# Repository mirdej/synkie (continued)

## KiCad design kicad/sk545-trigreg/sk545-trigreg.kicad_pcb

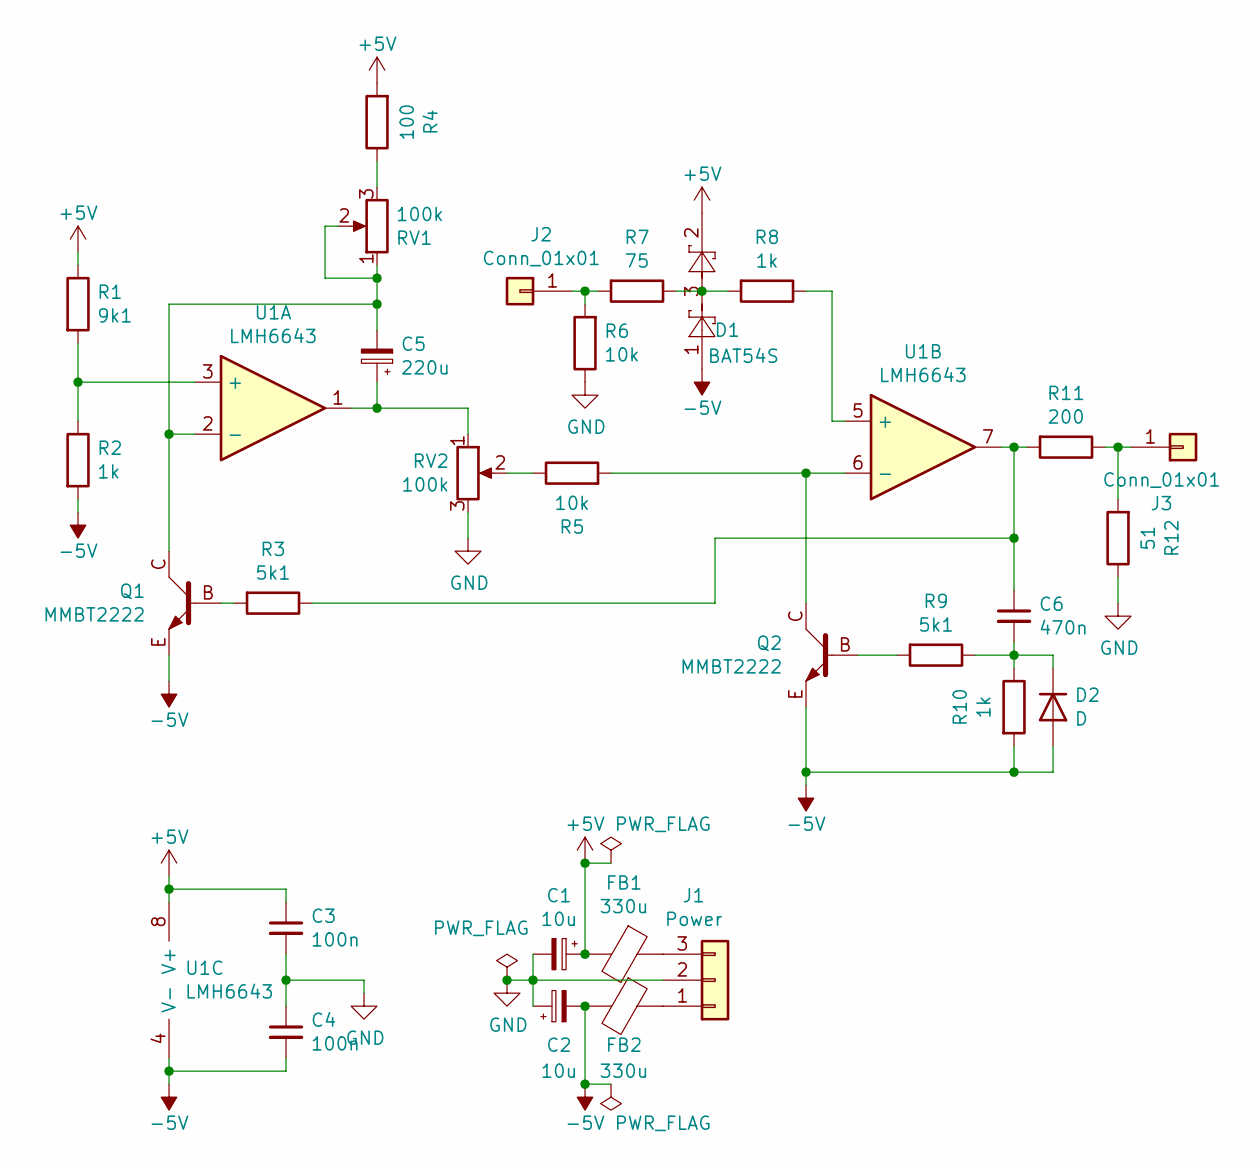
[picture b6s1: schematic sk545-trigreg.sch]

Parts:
C1, C2: 10u; CP_EIA-3528-21_Kemet-B_Pad1.50x2.35mm_HandSolder
C3, C4: 100n; C_0805_2012Metric_Pad1.15x1.40mm_HandSolder
C5: 220u; CP_EIA-7361-38_AVX-V_Pad2.18x3.30mm_HandSolder
C6: 470n; C_0805_2012Metric_Pad1.15x1.40mm_HandSolder
D1: BAT54S; SOT-23
D2: D; D_SOT-23_ANK
FB1, FB2: 330u; L_1206_3216Metric_Pad1.42x1.75mm_HandSolder
J1: Power; Molex_KK-254_AE-6410-03A_1x03_P2.54mm_Vertical
J2, J3: Conn_01x01; Solderpad_1mm
Q1, Q2: MMBT2222; SOT-23_BEC
R1: 9k1; R_0805_2012Metric_Pad1.15x1.40mm_HandSolder
R2, R8, R10: 1k; R_0805_2012Metric_Pad1.15x1.40mm_HandSolder
R3, R9: 5k1; R_0805_2012Metric_Pad1.15x1.40mm_HandSolder
R4: 100; R_0805_2012Metric_Pad1.15x1.40mm_HandSolder
R5, R6: 10k; R_0805_2012Metric_Pad1.15x1.40mm_HandSolder
R7: 75; R_0805_2012Metric_Pad1.15x1.40mm_HandSolder
R11: 200; R_0805_2012Metric_Pad1.15x1.40mm_HandSolder
R12: 51; R_0805_2012Metric_Pad1.15x1.40mm_HandSolder
RV1, RV2: 100k; Potentiometer_Uwe_100k
U1: LMH6643; SOIC-8_3.9x4.9mm_P1.27mm

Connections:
+5V: C1.1, C3.1, D1.2, FB1.2, R1.1, R4.2, U1.8 (V+)
-5V: C2.2, C4.2, D1.1, D2.2 (A), FB2.2, Q1.E, Q2.E, R2.2, R10.2, U1.4 (V-)
GND: C1.2, C2.1, C3.2, C4.1, J1.2, R6.1, R12.1, RV2.3
unnamed: C5.1, RV2.1, U1.1
unnamed: C5.2, Q1.C, RV1.1, RV1.2, U1.2 (-)
unnamed: C6.1, R3.1, R11.2, U1.7
unnamed: C6.2, D2.1 (K), R9.1, R10.1
unnamed: D1.3, R7.1, R8.2
unnamed: FB1.1, J1.3
unnamed: FB2.1, J1.1
unnamed: J2.1, R6.2, R7.2
unnamed: J3.1, R11.1, R12.2
unnamed: Q1.B, R3.2
unnamed: Q2.B, R9.2
unnamed: Q2.C, R5.2, U1.6 (-)
unnamed: R1.2, R2.1, U1.3 (+)
unnamed: R4.1, RV1.3
unnamed: R5.1, RV2.2
unnamed: R8.1, U1.5 (+)

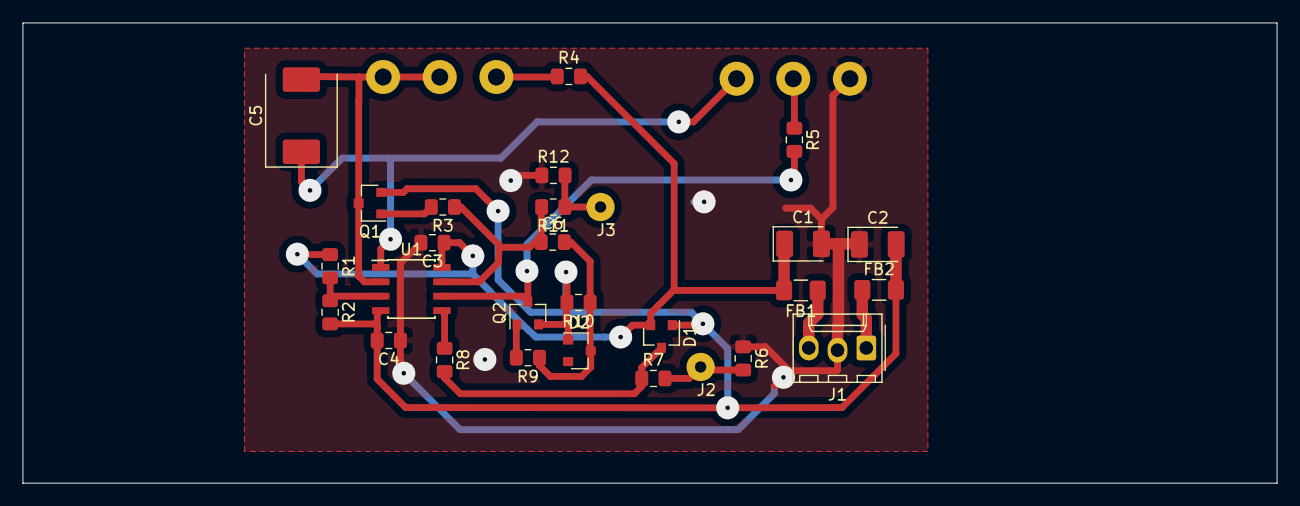
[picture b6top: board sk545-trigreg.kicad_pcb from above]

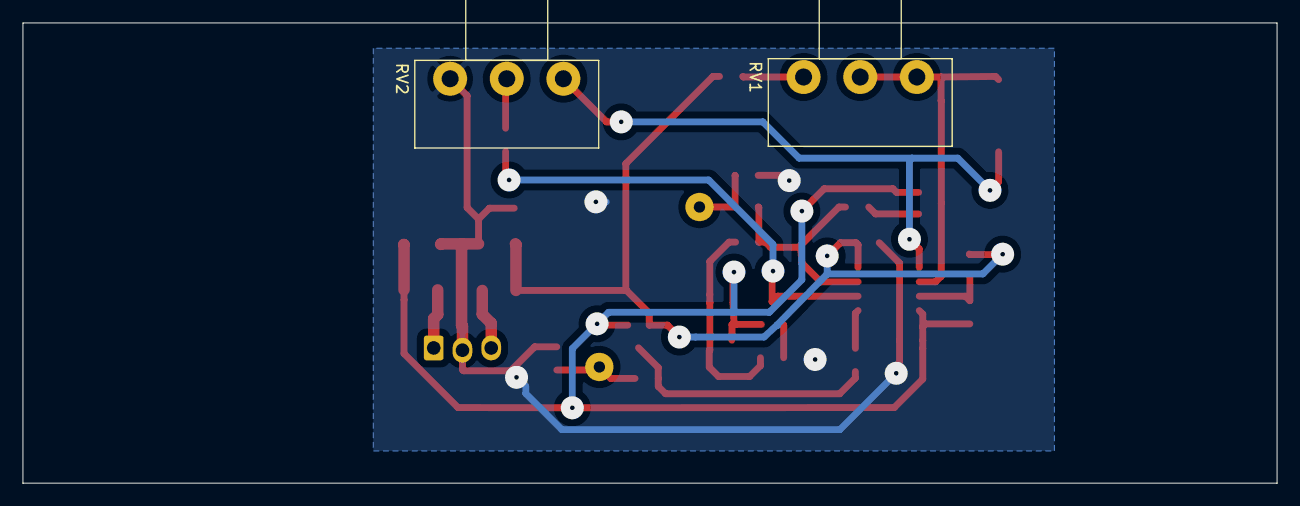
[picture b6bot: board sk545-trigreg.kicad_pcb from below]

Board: 2 copper layers, 110.7 x 40.6 mm, 30 parts (2 on the bottom side), 19 nets.

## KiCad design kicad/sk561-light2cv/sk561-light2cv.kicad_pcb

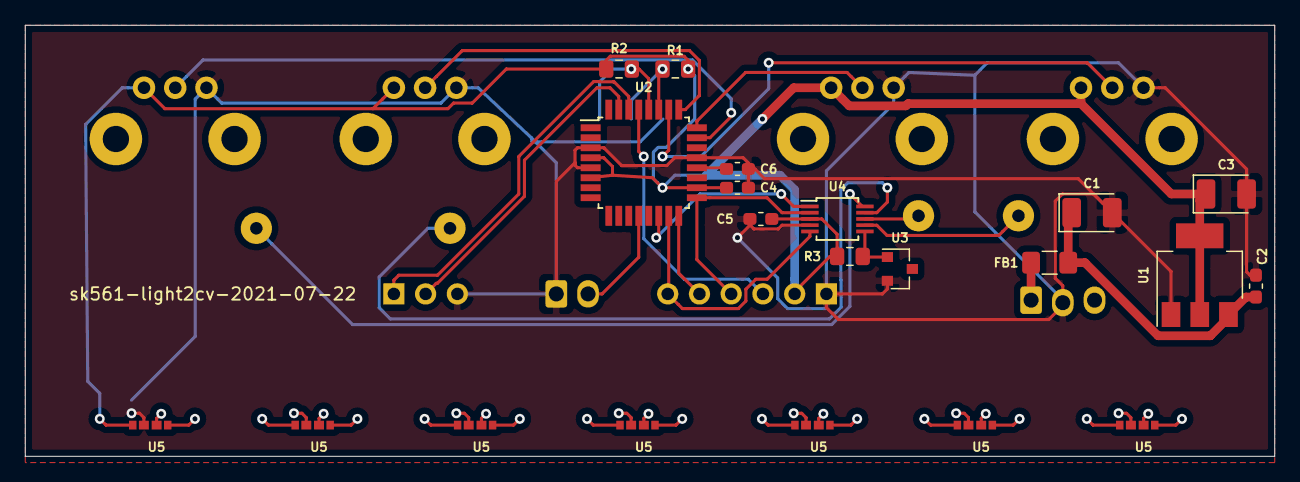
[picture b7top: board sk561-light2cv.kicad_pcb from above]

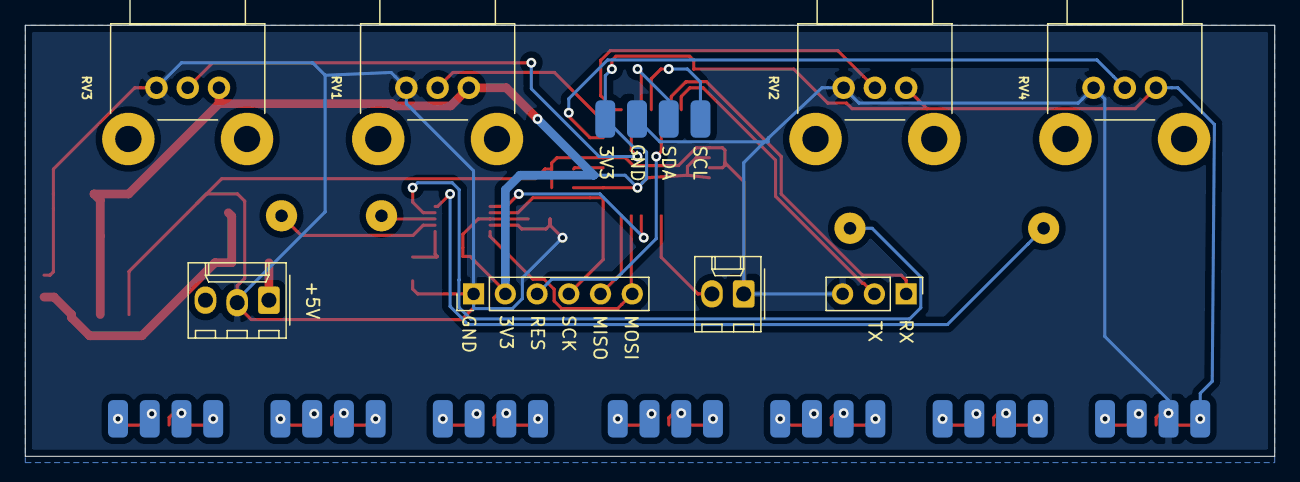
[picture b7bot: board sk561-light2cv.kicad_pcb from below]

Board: 2 copper layers, 100.0 x 34.5 mm, 41 parts (16 on the bottom side), 26 nets.

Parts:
C1, C3: 10u; CP_EIA-3528-21_Kemet-B_Pad1.50x2.35mm_HandSolder
C2, C4, C5, C6: 100n; C_0603_1608Metric_Pad1.05x0.95mm_HandSolder
FB1: Ferrite_Bead; L_1206_3216Metric_Pad1.42x1.75mm_HandSolder
J1: Conn_01x03; Molex_KK-254_AE-6410-03A_1x03_P2.54mm_Vertical
J2: switch; Molex_KK-254_AE-6410-02A_1x02_P2.54mm_Vertical
J3, J5, J6, J7: Conn_01x01; Solderpad_1mm
J4: Serial; PinHeader_1x03_P2.54mm_Vertical
J8: int; smd-4pin
J9, J9#2, J9#3, J9#4, J9#5, J9#6, J9#7: Conn_01x04; smd-4pin
R1, R2: 4k7; R_0805_2012Metric_Pad1.15x1.40mm_HandSolder
R3: 560; R_0805_2012Metric_Pad1.15x1.40mm_HandSolder
RV1, RV2, RV3, RV4: R_POT; Potentiometer_Alps_RK09L_Single_Horizontal
U1: AZ1117-3.3; SOT-223-3_TabPin2
U2: ATmega88-20AU; TQFP-32_7x7mm_P0.8mm
U3: ADR510; SOT-23
U4: MAX5741; MSOP-10_3x3mm_P0.5mm
U5, U5#2, U5#3, U5#4, U5#5, U5#6, U5#7: VEML3328; VEML3328SL
U7: AnymaISP; PinHeader_1x06_P2.54mm_Vertical

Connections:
+3V3: C3.1, C4.1, C5.1, J8.1, J9#7.1, R1.1, R2.1, R3.1, RV1.1, RV2.1, RV3.1, RV4.1, U1.2, U2.4, U2.6, U2.18, U4.3, U5#7.1, U7.2
+5V: C1.1, C2.1, FB1.1, U1.3
/a: RV4.2, U2.23
/b: RV1.2, U2.24
/c: RV2.2, U2.25
/cs: U2.14, U4.1
/d: RV3.2, U2.26
/miso: U2.16, U7.5
/mosi: U2.15, U4.5, U7.6
/reset: U2.29, U7.3
/sck: U2.17, U4.2, U7.4
/scl: J9#7.4, U5#7.4
/scl_1: J8.4, R2.2, U2.28
/sda: J9#7.3, U5#7.3
/sda_1: J8.3, R1.2, U2.27
GND: C1.2, C2.2, C3.2, C4.2, C5.2, C6.2, J1.2, J2.1, J4.3, J8.2, J9#7.2, RV1.3, RV2.3, RV3.3, RV4.3, U1.1, U2.3, U2.5, U2.21, U3.2, U4.4, U5#7.2, U7.1
unnamed: C6.1, U2.20
unnamed: FB1.2, J1.1
unnamed: J2.2, U2.12
unnamed: J3.1, U4.7
unnamed: J4.1, U2.30
unnamed: J4.2, U2.31
unnamed: J5.1, U4.8
unnamed: J6.1, U4.9
unnamed: J7.1, U4.10
unnamed: R3.2, U3.1, U4.6

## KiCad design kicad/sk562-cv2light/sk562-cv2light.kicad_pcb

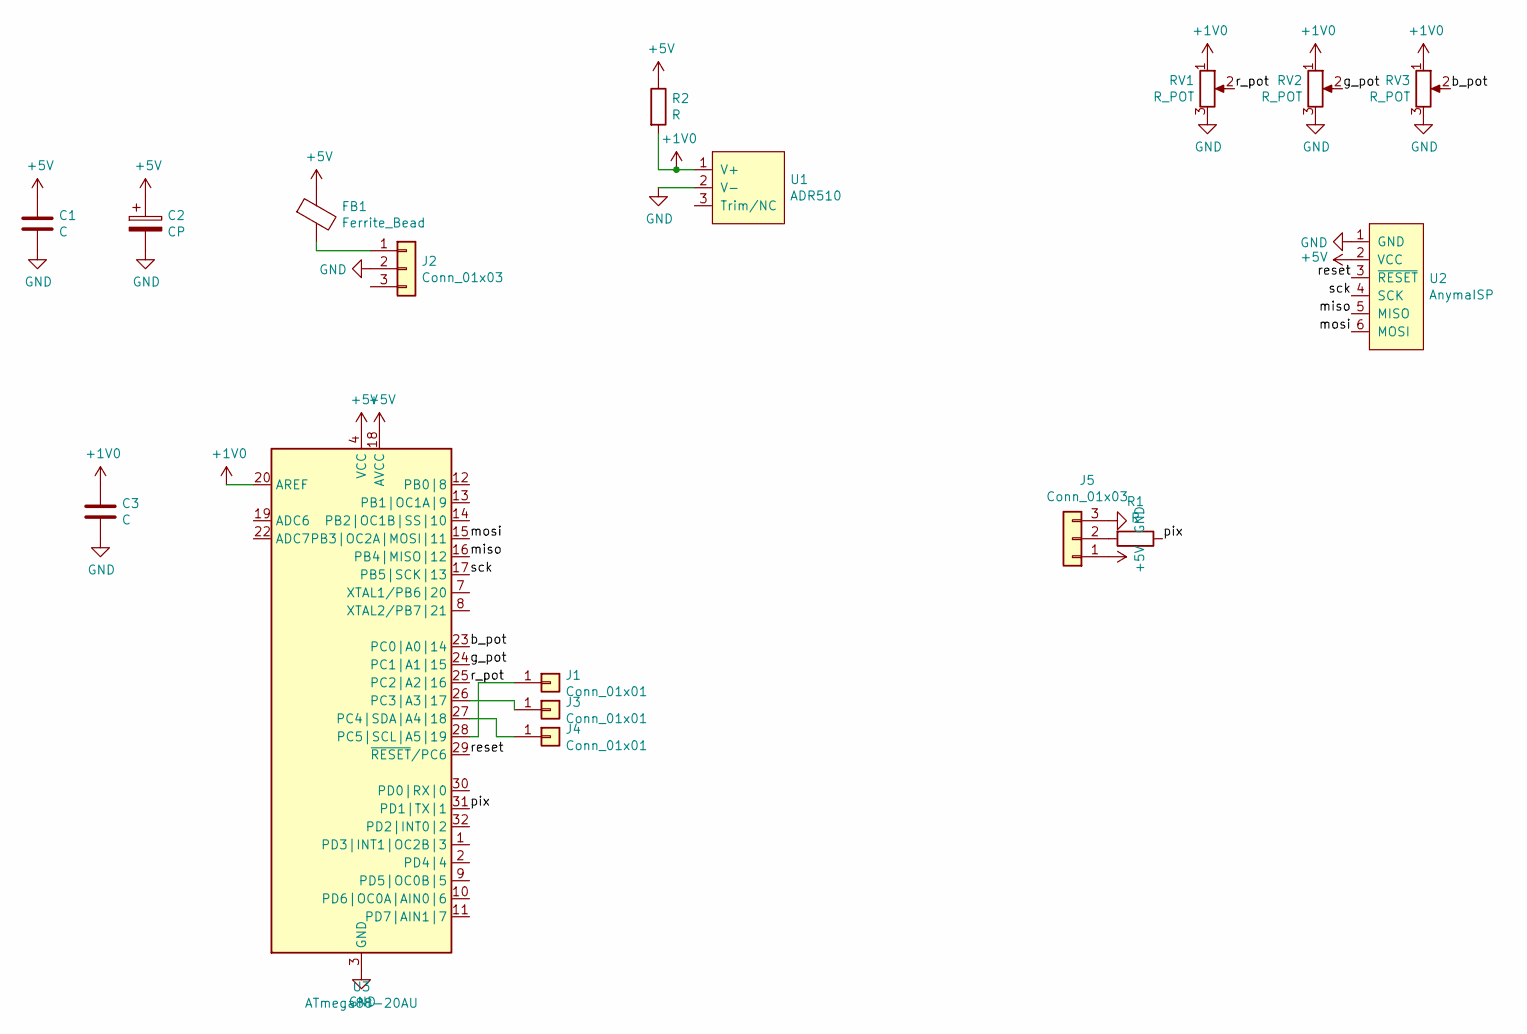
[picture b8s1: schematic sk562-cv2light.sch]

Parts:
C1, C3: C; C_0603_1608Metric_Pad1.05x0.95mm_HandSolder
C2: CP; CP_EIA-3528-21_Kemet-B_Pad1.50x2.35mm_HandSolder
FB1: Ferrite_Bead; C_0805_2012Metric_Pad1.15x1.40mm_HandSolder
J1, J3, J4: Conn_01x01; Solderpad_1mm
J2, J5: Conn_01x03; PinHeader_1x03_P2.54mm_Vertical
R1, R2: R; R_0805_2012Metric_Pad1.15x1.40mm_HandSolder
RV1, RV2, RV3: R_POT; Potentiometer_Uwe_100k
U1: ADR510; SOT-23
U2: AnymaISP; Pinhead_SMD_6
U3: ATmega88-20AU; TQFP-32_7x7mm_P0.8mm

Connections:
+1V0: C3.1, R2.2, RV1.1, RV2.1, RV3.1, U1.1 (V+), U3.20 (AREF)
+5V: C1.1, C2.1, FB1.1, J5.1, R2.1, U2.2 (VCC), U3.4 (VCC), U3.6 (VCC), U3.18 (AVCC)
/b_pot: RV3.2, U3.23 (PC0|A0|14)
/g_pot: RV2.2, U3.24 (PC1|A1|15)
/miso: U2.5 (MISO), U3.16 (PB4|MISO|12)
/mosi: U2.6 (MOSI), U3.15 (PB3|OC2A|MOSI|11)
/pix: R1.1, U3.31 (PD1|TX|1)
/r_pot: RV1.2, U3.25 (PC2|A2|16)
/reset: U2.3 (~RESET), U3.29 (~RESET~/PC6)
/sck: U2.4 (SCK), U3.17 (PB5|SCK|13)
GND: C1.2, C2.2, C3.2, J2.2, J5.3, RV1.3, RV2.3, RV3.3, U1.2 (V-), U2.1 (GND), U3.3 (GND), U3.5 (GND), U3.21 (GND)
unnamed: FB1.2, J2.1
unnamed: J1.1, U3.28 (PC5|SCL|A5|19)
unnamed: J3.1, U3.26 (PC3|A3|17)
unnamed: J4.1, U3.27 (PC4|SDA|A4|18)
unnamed: J5.2, R1.2

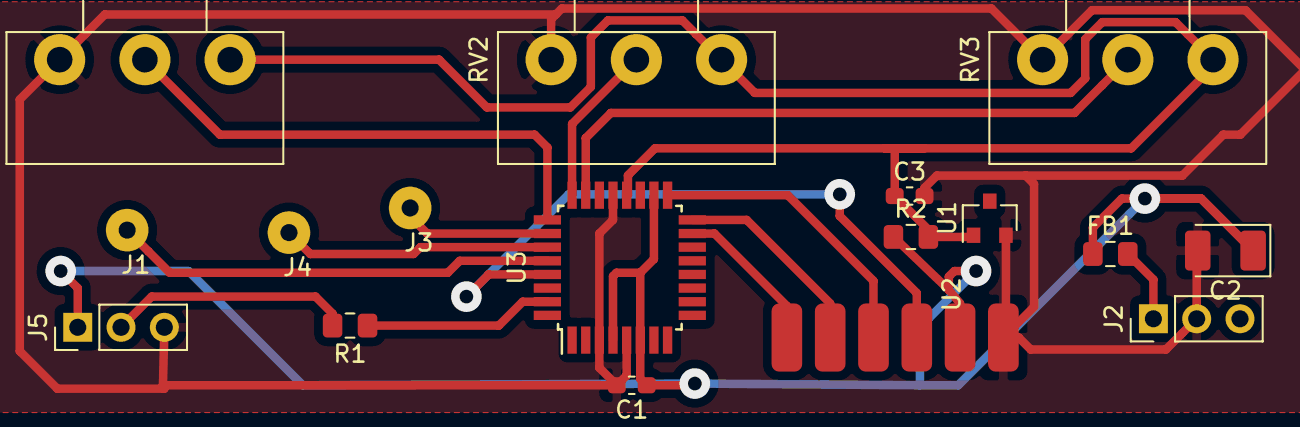
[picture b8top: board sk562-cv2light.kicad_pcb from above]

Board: 2 copper layers, 17 parts (0 on the bottom side), 16 nets.
